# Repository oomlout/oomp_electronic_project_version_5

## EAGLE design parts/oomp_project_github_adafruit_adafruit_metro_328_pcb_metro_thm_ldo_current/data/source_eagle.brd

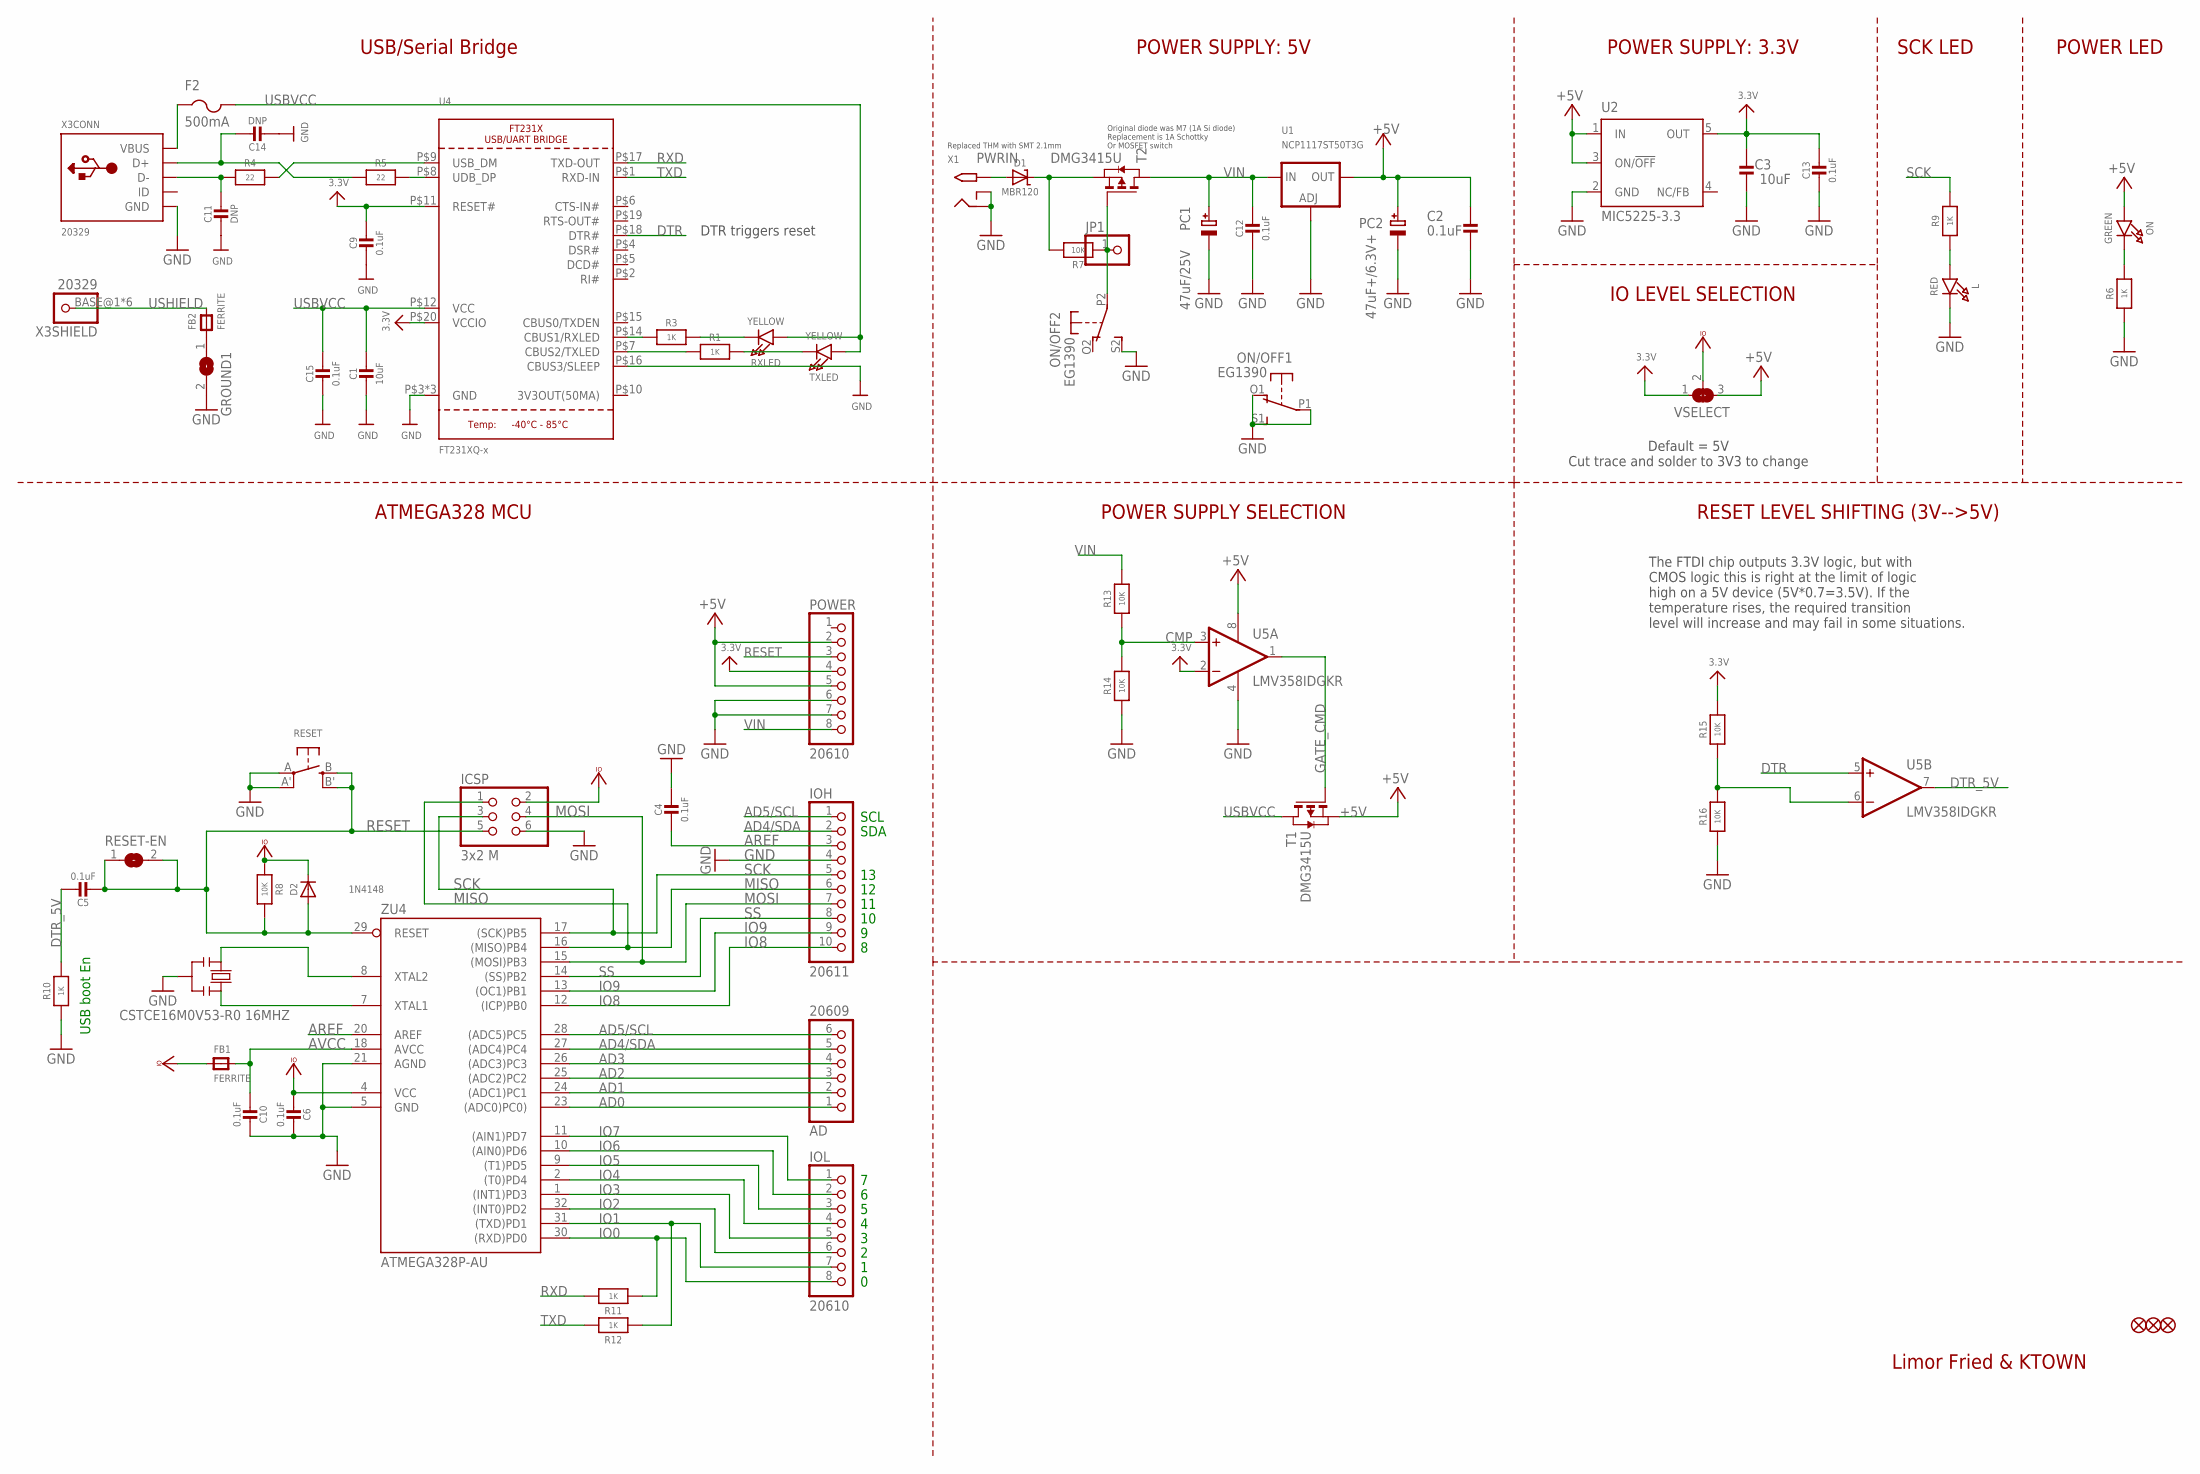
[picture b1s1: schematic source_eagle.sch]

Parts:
AD: 20609; 1X06_OVAL
C1, C3: 10uF; 0805-NO
C2, C4, C5, C6, C9, C12, C13, C15: 0.1uF; 0805-NO
C10: 0.1uF; 0805_10MGAP
C11, C14: DNP; 0805-NO
D1: MBR120; SOD-123
D2: 1N4148; SOD-323
F2: 500mA; R1206
FB1, FB2: FERRITE; 0805-NO
FD1, FD2, FD3: FIDUCIAL""; FIDUCIAL_1MM
GROUND1: SJ
ICSP: 3x2 M; 2X03_ROUND_70MIL
IOH: 20611; 1X10_OVAL
IOL: 20610; 1X08_OVAL
JP1: HEADER-1X1ROUND; 1X01_ROUND
L: RED; CHIPLED_0805_NOOUTLINE
ON: GREEN; CHIPLED_0805_NOOUTLINE
ON/OFF: EG1390
PC1: 47uF/25V; PANASONIC_D
PC2: 47uF+/6.3V+; PANASONIC_D
POWER: 20610; 1X08_OVAL
R1, R3, R6, R9, R10, R11, R12: 1K; 0805-NO
R4, R5: 22; 0805-NO
R7, R13, R14, R15, R16: 10K; 0805-NO
R8: 10K; _0805MP
RESET: SWITCH_TACT_SMT; EVQ-Q2
RESET-EN: SJ
RXLED: YELLOW; CHIPLED_0805_NOOUTLINE
T1, T2: DMG3415U; SOT-23
TXLED: YELLOW; CHIPLED_0805_NOOUTLINE
U1: NCP1117ST50T3G; SOT223-R
U2: MIC5225-3.3; SOT23-DBV
U4: FT231XQ-x; QFN20_4MM
U5: LMV358IDGKR; MSOP08
VSELECT: SOLDERJUMPER_2WAY; SOLDERJUMPER_2WAY_OPEN_NOPASTE
X1: 2.1MMJACKSMT; DCJACK_2MM_SMT
X3: 20329; 4UCONN_20329
Y2: CSTCE16M0V53-R0 16MHZ; RESONATOR
ZU4: ATMEGA328P-AU; TQFP32-08

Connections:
3.3V: C3.2, C9.1, C13.1, POWER.4, R15.2, U2.5 (OUT), U4.P$11 (RESET#), U4.P$20 (VCCIO), U5.2 (-IN), VSELECT.1
3V3OUT(50MA): U4.P$10 (3V3OUT(50MA))
+5V: C2.2, ON.A, PC2.+, POWER.2, POWER.5, T1.2 (S), U1.2 (OUT), U1.4 (OUT), U2.1 (IN), U2.3 (ON/!OFF), U5.8 (V+), VSELECT.3
AD0: AD.1, ZU4.23 ((ADC0)PC0))
AD1: AD.2, ZU4.24 ((ADC1)PC1)
AD2: AD.3, ZU4.25 ((ADC2)PC2)
AD3: AD.4, ZU4.26 ((ADC3)PC3)
AD4/SDA: AD.5, IOH.2, ZU4.27 ((ADC4)PC4)
AD5/SCL: AD.6, IOH.1, ZU4.28 ((ADC5)PC5)
AREF: C4.2, IOH.3, ZU4.20 (AREF)
AVCC: C10.2, FB1.2, ZU4.18 (AVCC)
CMP: R13.1, R14.2, U5.3 (+IN)
D+: C14.1, R5.1, X3.D+
D-: C11.1, R4.1, X3.D-
DTR: U4.P$18 (DTR#), U5.5 (+IN)
DTR_5V: C5.1, R10.2, U5.7 (OUT)
GATE_CMD: T1.3 (G), U5.1 (OUT)
GND: C1.2, C2.1, C3.1, C4.1, C6.1, C9.2, C10.1, C11.2, C12.2, C13.2, C14.2, C15.2, GROUND1.2, ICSP.6, IOH.4, L.C, ON/OFF.O1 (O), ON/OFF.P1, ON/OFF.S1 (S), ON/OFF.S2 (S), PC1.-, PC2.-, POWER.6, POWER.7, R6.1, R10.1, R14.1, R16.1, RESET.A, RESET.A' (P1), U1.1 (ADJ), U2.2 (GND), U4.P$3 (GND), U4.P$13 (GND), U4.P$16 (CBUS3/SLEEP), U4.P$21 (GND), U5.4 (V-), X1.GND (RING), X1.GNDBREAK (RING_SW), X3.GND, Y2.2, ZU4.5 (GND), ZU4.21 (AGND)
IO0: IOL.8, R11.1, ZU4.30 ((RXD)PD0)
IO1: IOL.7, R12.1, ZU4.31 ((TXD)PD1)
IO2: IOL.6, ZU4.32 ((INT0)PD2)
IO3: IOL.5, ZU4.1 ((INT1)PD3)
IO4: IOL.4, ZU4.2 ((T0)PD4)
IO5: IOL.3, ZU4.9 ((T1)PD5)
IO6: IOL.2, ZU4.10 ((AIN0)PD6)
IO7: IOL.1, ZU4.11 ((AIN1)PD7)
IO8: IOH.10, ZU4.12 ((ICP)PB0)
IO9: IOH.9, ZU4.13 ((OC1)PB1)
MISO: ICSP.1, IOH.6, ZU4.16 ((MISO)PB4)
MOSI: ICSP.4, IOH.7, ZU4.15 ((MOSI)PB3)
unnamed: L.A, R9.1
unnamed: FB2.1, GROUND1.1
unnamed: ON.C, R6.2
unnamed: R3.2, U4.P$14 (CBUS1/RXLED)
unnamed: R3.1, RXLED.C
unnamed: R1.2, U4.P$7 (CBUS2/TXLED)
unnamed: R1.1, TXLED.C
unnamed: R4.2, U4.P$9 (USB_DM)
unnamed: R5.2, U4.P$8 (UDB_DP)
unnamed: R15.1, R16.2, U5.6 (-IN)
unnamed: JP1.1, ON/OFF.P2, R7.1, T2.3 (G)
unnamed: D1.C, R7.2, T2.2 (S)
PWRIN: D1.A, X1.PWR2 (TIP)
RESET: C5.2, D2.A, ICSP.5, POWER.3, R8.1, RESET.B (S), RESET.B' (S1), RESET-EN.1, RESET-EN.2, ZU4.29 (RESET)
RXD: R11.2, U4.P$17 (TXD-OUT)
SCK: ICSP.3, IOH.5, R9.2, ZU4.17 ((SCK)PB5)
SS: IOH.8, ZU4.14 ((SS)PB2)
TXD: R12.2, U4.P$1 (RXD-IN)
USBVCC: C1.1, C15.1, F2.2, RXLED.A, T1.1 (D), TXLED.A, U4.P$12 (VCC)
USHIELD: FB2.2, X3.BASE@1 (1), X3.BASE@2 (1), X3.SPRT@1 (1), X3.SPRT@2 (1), X3.SPRT@3 (1), X3.SPRT@4 (1)
VBUS: F2.1, X3.VBUS
VCCIO: C6.2, D2.C, FB1.1, ICSP.2, R8.2, VSELECT.2, ZU4.4 (VCC)
VIN: C12.1, PC1.+, POWER.8, R13.2, T2.1 (D), U1.3 (IN)
XTAL1: Y2.3, ZU4.7 (XTAL1)
XTAL2: Y2.1, ZU4.8 (XTAL2)

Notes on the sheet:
USB boot En
SDA
SCL
Limor Fried & KTOWN
Original diode was M7 (1A Si diode) Replacement is 1A Schottky Or MOSFET switch
Replaced THM with SMT 2.1mm
POWER SUPPLY: 5V
USB/Serial Bridge
POWER SUPPLY: 3.3V
IO LEVEL SELECTION
POWER LED
ATMEGA328 MCU
POWER SUPPLY SELECTION
SCK LED
Default = 5V Cut trace and solder to 3V3 to change
RESET LEVEL SHIFTING (3V-->5V)
The FTDI chip outputs 3.3V logic, but with CMOS logic this is right at the limit of logic high on a 5V device (5V*0.7=3.5V). If the temperature rises, the required transition level will increase and may fail in some situations.
DTR triggers reset

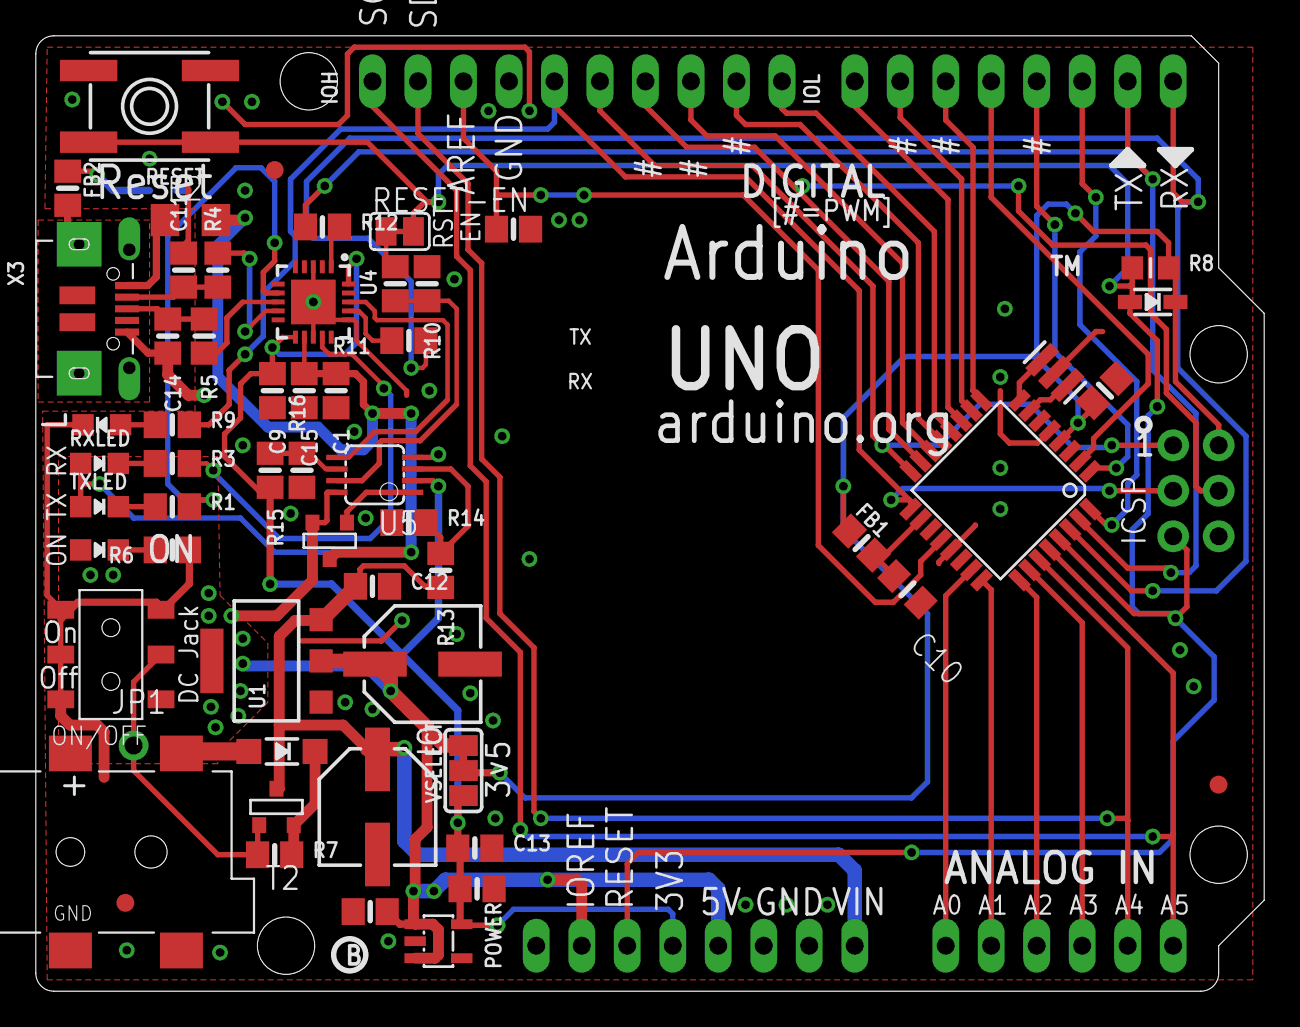
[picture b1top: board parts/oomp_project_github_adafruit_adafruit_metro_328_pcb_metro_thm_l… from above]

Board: 2 copper layers, 68.6 x 53.3 mm, 66 parts (1 on the bottom side), 54 nets.

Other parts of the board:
U$11: METROSILK_TOP
U$14: METROSILK_BOT
U$15: PCBFEAT-REV-040

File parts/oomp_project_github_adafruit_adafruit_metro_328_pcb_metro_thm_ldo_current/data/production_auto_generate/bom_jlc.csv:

Comment,Designator,Footprint,LCSC Part #
,JP1,Metro THM+LDO Rev B-import-fps:1X01_ROUND,C7501259
,RESET0,Metro THM+LDO Rev B-import-fps:EVQ-Q2,
,U$14,Metro THM+LDO Rev B-import-fps:METROSILK_BOT,
,U$11,Metro THM+LDO Rev B-import-fps:METROSILK_TOP,
,U$15,Metro THM+LDO Rev B-import-fps:PCBFEAT-REV-040,
,"GROUND1,RESET-EN0",Metro THM+LDO Rev B-import-fps:SJ,
,VSELECT0,Metro THM+LDO Rev B-import-fps:SOLDERJUMPER_2WAY_OPEN_NOPASTE,
0.1uF,"C2,C4,C5,C6,C9,C12,C13,C15",Metro THM+LDO Rev B-import-fps:0805-NO,
0.1uF,C10,Metro THM+LDO Rev B-import-fps:0805_10MGAP,
10K,"R7,R13,R14,R15,R16",Metro THM+LDO Rev B-import-fps:0805-NO,C17414
10K,R8,Metro THM+LDO Rev B-import-fps:_0805MP,C17414
10uF,"C1,C3",Metro THM+LDO Rev B-import-fps:0805-NO,
1K,"R1,R3,R6,R9,R10,R11,R12",Metro THM+LDO Rev B-import-fps:0805-NO,C17513
1N4148,D2,Metro THM+LDO Rev B-import-fps:SOD-323,
2.1MMJACKSMT,X1,Metro THM+LDO Rev B-import-fps:DCJACK_2MM_SMT,
20329,X3,Metro THM+LDO Rev B-import-fps:4UCONN_20329,
20609,AD0,Metro THM+LDO Rev B-import-fps:1X06_OVAL,C37208
20610,"IOL0,POWER0",Metro THM+LDO Rev B-import-fps:1X08_OVAL,C492421
20611,IOH0,Metro THM+LDO Rev B-import-fps:1X10_OVAL,C57369
22,"R4,R5",Metro THM+LDO Rev B-import-fps:0805-NO,C2907310
3x2 M,ICSP0,Metro THM+LDO Rev B-import-fps:2X03_ROUND_70MIL,
47uF+/6.3V+,PC2,Metro THM+LDO Rev B-import-fps:PANASONIC_D,
47uF/25V,PC1,Metro THM+LDO Rev B-import-fps:PANASONIC_D,
500mA,F2,Metro THM+LDO Rev B-import-fps:R1206,
ATMEGA328P-AU,ZU4,Metro THM+LDO Rev B-import-fps:TQFP32-08,
CSTCE16M0V53-R0 16MHZ,Y2,Metro THM+LDO Rev B-import-fps:RESONATOR,
DMG3415U,"T1,T2",Metro THM+LDO Rev B-import-fps:SOT-23,
DNP,"C11,C14",Metro THM+LDO Rev B-import-fps:0805-NO,
EG1390,ON/OFF0,Metro THM+LDO Rev B-import-fps:EG1390,
FERRITE,"FB1,FB2",Metro THM+LDO Rev B-import-fps:0805-NO,
"FIDUCIAL""""","FD1,FD2,FD3",Metro THM+LDO Rev B-import-fps:FIDUCIAL_1MM,
FT231XQ-x ,U4,Metro THM+LDO Rev B-import-fps:QFN20_4MM,
GREEN,ON0,Metro THM+LDO Rev B-import-fps:CHIPLED_0805_NOOUTLINE,
LMV358IDGKR,U5,Metro THM+LDO Rev B-import-fps:MSOP08,
MBR120,D1,Metro THM+LDO Rev B-import-fps:SOD-123,
MIC5225-3.3,U2,Metro THM+LDO Rev B-import-fps:SOT23-DBV,
NCP1117ST50T3G,U1,Metro THM+LDO Rev B-import-fps:SOT223-R,
RED,L0,Metro THM+LDO Rev B-import-fps:CHIPLED_0805_NOOUTLINE,
YELLOW,"RXLED0,TXLED0",Metro THM+LDO Rev B-import-fps:CHIPLED_0805_NOOUTLINE,

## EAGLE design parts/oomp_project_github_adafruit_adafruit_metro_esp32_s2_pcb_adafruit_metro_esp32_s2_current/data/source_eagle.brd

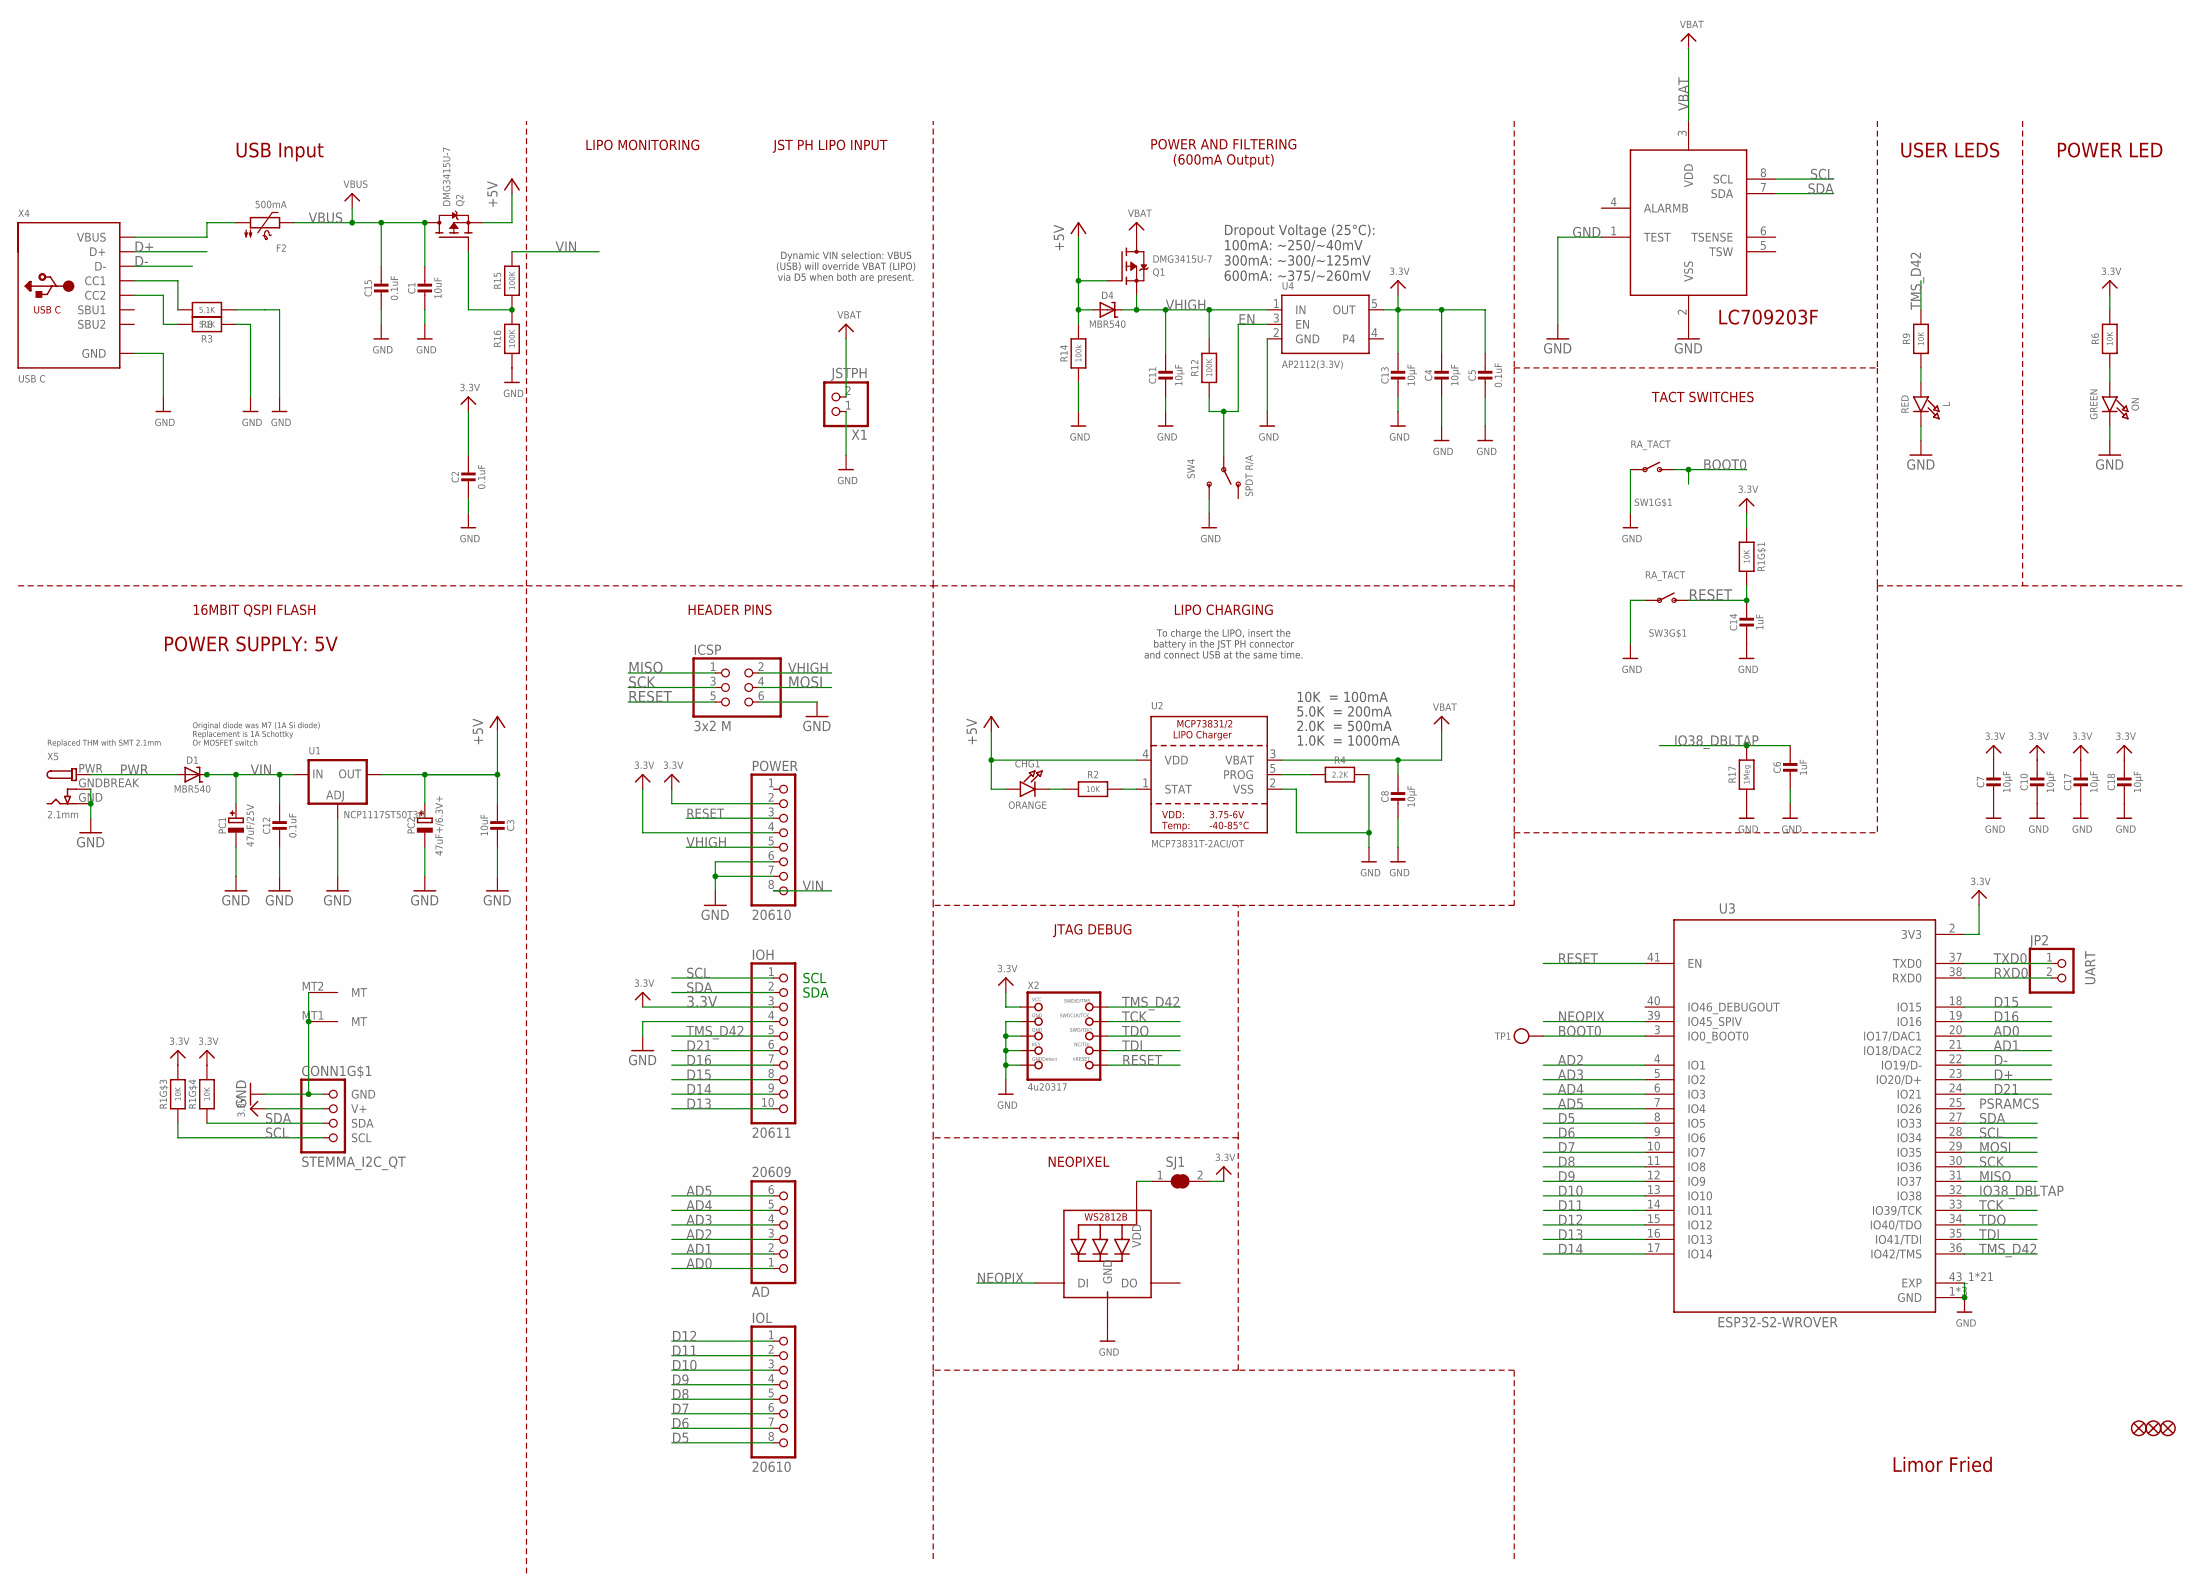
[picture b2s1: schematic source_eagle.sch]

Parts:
AD: 20609; 1X06_OVALWAVE
C1, C3: 10uF; 0805-NO
C2, C5, C12, C15: 0.1uF; 0603-NO
C4, C7, C8, C10, C11, C13, C17, C18: 10µF; 0805-NO
C6, C14: 1uF; 0603-NO
CHG1: ORANGE; CHIPLED_0603_NOOUTLINE
CONN1: STEMMA_I2C_QT; JST_SH4
D1, D4: MBR540; SOD-123
F2: 500mA; 1206
FD1, FD2, FD3: FIDUCIAL_1MM
IC2: LC709203F; WDFN8_3X4_0.65
ICSP: 3x2 M; 2X03_ROUND_70MIL
IOH: 20611; 1X10_OVALWAVE
IOL: 20610; 1X08_OVALWAVE
JP2: UART; 1X02_ROUND
L: RED; CHIPLED_0603_NOOUTLINE
LED1: WS2812B3535; LED3535
ON: GREEN; CHIPLED_0603_NOOUTLINE
PC1: 47uF/25V; PANASONIC_D
PC2: 47uF+/6.3V+; PANASONIC_D
POWER: 20610; 1X08_OVALWAVE
Q1, Q2: DMG3415U-7; SOT23-R
R1: 10K; RESPACK_4X0603
R2, R6, R9: 10K; 0603-NO
R3, R8: 5.1K; 0603-NO
R4: 2.2K; 0603-NO
R12, R15, R16: 100K; 0603-NO
R14: 100k; 0603-NO
R17: 1Meg; 0603-NO
SJ1: SOLDERJUMPER_CLOSED; SOLDERJUMPER_CLOSEDWIRE
SW1, SW3: RA_TACT; SPST_TACTILE_RA
SW4: SPDT R/A; SPDT_SMT_SSSS811101
TP1: TESTPOINTROUND1.5MMNO; TESTPOINT_ROUND_1.5MM_NO
U1: NCP1117ST50T3G; SOT223-R
U2: MCP73831T-2ACI/OT; SOT23-5
U3: ESP32-S2-WROVER; MODULE_ESP32-S2-WROVER
U4: AP2112(3.3V); SOT23-5
X1: JSTPH; JSTPH2_BATT
X2: 4u20317; 2X05_1.27MM_BOX_POSTS
X4: USB C; USB_C_CUSB31-CFM2AX-01-X
X5: 2.1mm; DCJACK_2MM_PTH

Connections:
3.3V: C2.1, C4.1, C5.1, C7.1, C10.1, C13.1, C17.1, C18.1, CONN1.2 (V+), IOH.3, POWER.2, POWER.4, R1.1, R1.5 (2), R1.6 (2), R6.2, SJ1.2, U3.2 (3V3), U4.5 (OUT), X2.1 (VCC)
+5V: C3.2, CHG1.A, D4.A, PC2.+, Q1.1 (G), Q2.2 (S), R14.2, U1.2 (OUT), U1.4 (OUT), U2.4 (VDD)
AD0: AD.1, U3.20 (IO17/DAC1)
AD1: AD.2, U3.21 (IO18/DAC2)
AD2: AD.3, U3.4 (IO1)
AD3: AD.4, U3.5 (IO2)
AD4: AD.5, U3.6 (IO3)
AD5: AD.6, U3.7 (IO4)
BOOT0: SW1.2 (S), TP1.P$1, U3.3 (IO0_BOOT0)
D5: IOL.8, U3.8 (IO5)
D6: IOL.7, U3.9 (IO6)
D7: IOL.6, U3.10 (IO7)
D8: IOL.5, U3.11 (IO8)
D9: IOL.4, U3.12 (IO9)
D10: IOL.3, U3.13 (IO10)
D11: IOL.2, U3.14 (IO11)
D12: IOL.1, U3.15 (IO12)
D13: IOH.10, U3.16 (IO13)
D14: IOH.9, U3.17 (IO14)
D15: IOH.8, U3.18 (IO15)
D16: IOH.7, U3.19 (IO16)
D21: IOH.6, U3.24 (IO21)
D+: U3.23 (IO20/D+), X4.A6 (D+), X4.B6 (D+)
D-: U3.22 (IO19/D-), X4.A7 (D-), X4.B7 (D-)
EN: R12.1, SW4.B, U4.3 (EN)
GND: C1.2, C2.2, C3.1, C4.2, C5.2, C6.2, C7.2, C8.2, C10.2, C11.2, C12.2, C13.2, C14.2, C15.2, C17.2, C18.2, CONN1.1 (GND), CONN1.MT1 (MT), CONN1.MT2 (MT), IC2.1 (TEST), IC2.2 (VSS), ICSP.6, IOH.4, L.C, LED1.4 (GND), ON.C, PC1.-, PC2.-, POWER.6, POWER.7, R3.1, R4.2, R8.1, R14.1, R16.1, R17.1, SW1.1, SW3.1, SW4.C (S), U1.1 (ADJ), U2.2 (VSS), U3.1 (GND), U3.26 (GND), U3.42 (GND), U3.43_1 (EXP), U3.43_2 (EXP), U3.43_3 (EXP), U3.43_4 (EXP), U3.43_5 (EXP), U3.43_6 (EXP), U3.43_7 (EXP), U3.43_8 (EXP), U3.43_9 (EXP), U3.43_10 (EXP), U3.43_11 (EXP), U3.43_12 (EXP), U3.43_13 (EXP), U3.43_14 (EXP), U3.43_15 (EXP), U3.43_16 (EXP), U3.43_17 (EXP), U3.43_18 (EXP), U3.43_19 (EXP), U3.43_20 (EXP), U3.43_21 (EXP), U4.2 (GND), X1.1, X2.3 (GND), X2.5 (GND), X2.7 (KEY), X2.9 (GNDDETECT), X4.A1B12 (GND), X4.B1A12 (GND), X5.GND, X5.GNDBREAK
IO38_DBLTAP: C6.1, R17.2, U3.32 (IO38)
MISO: ICSP.1, U3.31 (IO37)
MOSI: ICSP.4, U3.29 (IO35)
unnamed: L.A, R9.1
unnamed: Q2.1 (G), R15.1, R16.2
unnamed: ON.A, R6.1
unnamed: CHG1.C, R2.1
unnamed: LED1.2 (VDD), SJ1.1
unnamed: R2.2, U2.1 (STAT)
unnamed: R8.2, X4.A5 (CC1)
unnamed: R3.2, X4.B5 (CC2)
unnamed: R4.1, U2.5 (PROG)
unnamed: F2.1, X4.A4B9 (VBUS), X4.B4A9 (VBUS)
NEOPIX: LED1.1 (DI), U3.39 (IO45_SPIV)
PWR: D1.A, X5.PWR
RESET: C14.1, ICSP.5, POWER.3, R1.8 (2), SW3.2 (S), U3.41 (EN), X2.10 (NRESET)
RXD0: JP2.2, U3.38 (RXD0)
SCK: ICSP.3, U3.30 (IO36)
SCL: CONN1.4 (SCL), IC2.8 (SCL), IOH.1, R1.3 (1), U3.28 (IO34)
SDA: CONN1.3 (SDA), IC2.7 (SDA), IOH.2, R1.4 (1), U3.27 (IO33)
TCK: U3.33 (IO39/TCK), X2.4 (SWDCLK)
TDI: U3.35 (IO41/TDI), X2.8 (TDI)
TDO: U3.34 (IO40/TDO), X2.6 (SWO)
TMS_D42: IOH.5, R9.2, U3.36 (IO42/TMS), X2.2 (SWDIO)
TXD0: JP2.1, U3.37 (TXD0)
VBAT: C8.1, IC2.3 (VDD), Q1.3 (D), U2.3 (VBAT), X1.2
VBUS: C1.1, C15.1, F2.2, Q2.3 (D)
VHIGH: C11.1, D4.C, ICSP.2, POWER.5, Q1.2 (S), R12.2, U4.1 (IN)
VIN: C12.1, D1.C, PC1.+, POWER.8, R15.2, U1.3 (IN)

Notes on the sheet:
SDA
SCL
Limor Fried
USB Input
POWER LED
USER LEDS
10K = 100mA
5.0K = 200mA
2.0K = 500mA
1.0K = 1000mA
LIPO CHARGING
LIPO MONITORING
To charge the LIPO, insert the battery in the JST PH connector and connect USB at the same time.
POWER AND FILTERING (600mA Output)
JST PH LIPO INPUT
Dynamic VIN selection: VBUS (USB) will override VBAT (LIPO) via D5 when both are present.
Dropout Voltage (25°C): 100mA: ~250/~40mV 300mA: ~300/~125mV 600mA: ~375/~260mV
HEADER PINS
16MBIT QSPI FLASH
TACT SWITCHES
JTAG DEBUG
NEOPIXEL
Original diode was M7 (1A Si diode) Replacement is 1A Schottky Or MOSFET switch
Replaced THM with SMT 2.1mm
POWER SUPPLY: 5V
PSRAMCS

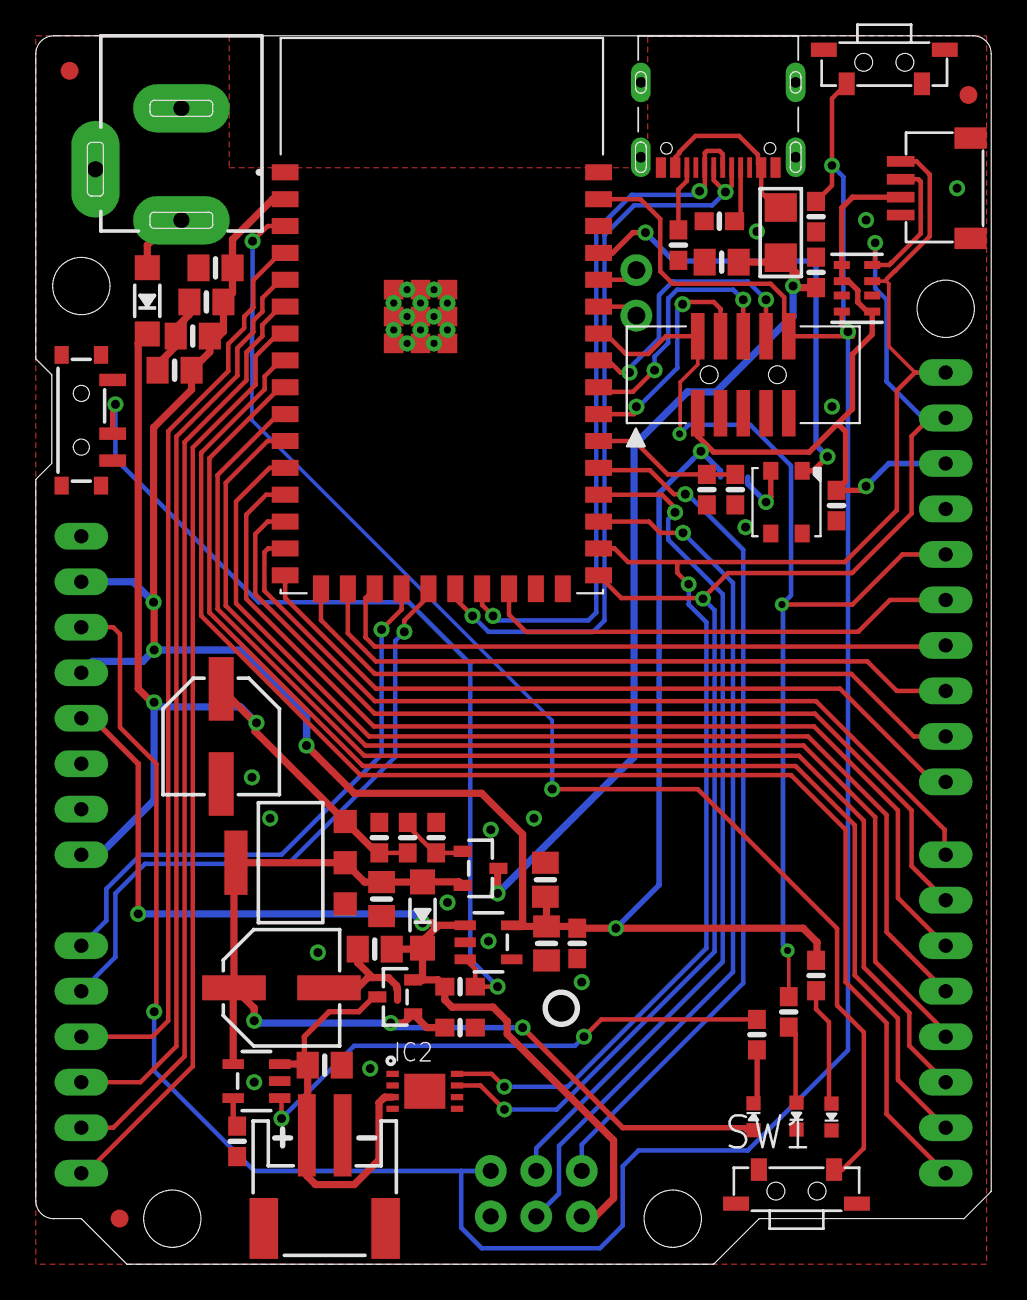
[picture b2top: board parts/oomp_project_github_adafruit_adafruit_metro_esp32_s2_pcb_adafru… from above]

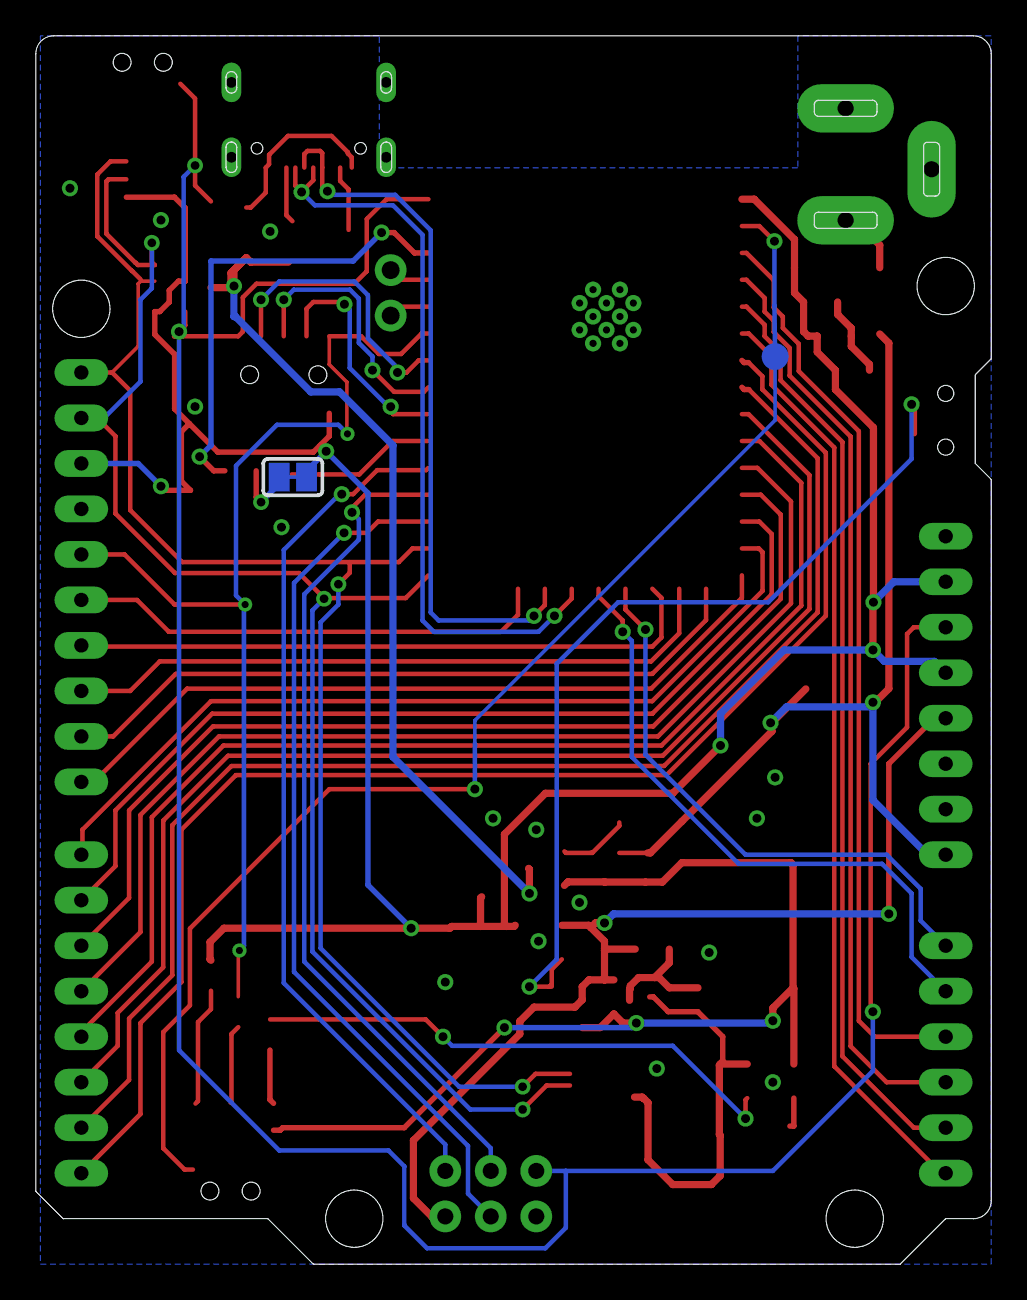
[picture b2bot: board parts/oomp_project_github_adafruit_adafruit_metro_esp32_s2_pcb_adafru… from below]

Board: 2 copper layers, 53.3 x 68.6 mm, 66 parts (3 on the bottom side), 55 nets.

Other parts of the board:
U$15: PCBFEAT-REV-040
U$52: ESP32S2_TOP
U$53: ESP32S2_BOT

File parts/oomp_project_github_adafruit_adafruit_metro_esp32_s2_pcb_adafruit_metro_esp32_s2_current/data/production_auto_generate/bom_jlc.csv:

Comment,Designator,Footprint,LCSC Part #
,U$53,Adafruit Metro ESP32-S2-import-fps:ESP32S2_BOT,
,U$52,Adafruit Metro ESP32-S2-import-fps:ESP32S2_TOP,
,U$15,Adafruit Metro ESP32-S2-import-fps:PCBFEAT-REV-040,
,TP1,Adafruit Metro ESP32-S2-import-fps:TESTPOINT_ROUND_1.5MM_NO,
0.1uF,"C2,C5,C12,C15",Adafruit Metro ESP32-S2-import-fps:0603-NO,C14663
100K,"R12,R15,R16",Adafruit Metro ESP32-S2-import-fps:0603-NO,C25803
100k,R14,Adafruit Metro ESP32-S2-import-fps:0603-NO,C25803
10K,"R2,R6,R9",Adafruit Metro ESP32-S2-import-fps:0603-NO,C98220
10K,R1,Adafruit Metro ESP32-S2-import-fps:RESPACK_4X0603,C98220
10uF,"C1,C3",Adafruit Metro ESP32-S2-import-fps:0805-NO,
10µF,"C4,C7,C8,C10,C11,C13,C17,C18",Adafruit Metro ESP32-S2-import-fps:0805-NO,
1Meg,R17,Adafruit Metro ESP32-S2-import-fps:0603-NO,C2907003
1uF,"C6,C14",Adafruit Metro ESP32-S2-import-fps:0603-NO,C5673
2.1mm,X5,Adafruit Metro ESP32-S2-import-fps:DCJACK_2MM_PTH,
2.2K,R4,Adafruit Metro ESP32-S2-import-fps:0603-NO,C4190
20609,AD0,Adafruit Metro ESP32-S2-import-fps:1X06_OVALWAVE,C37208
20610,"IOL0,POWER0",Adafruit Metro ESP32-S2-import-fps:1X08_OVALWAVE,C492421
20611,IOH0,Adafruit Metro ESP32-S2-import-fps:1X10_OVALWAVE,C57369
3x2 M,ICSP0,Adafruit Metro ESP32-S2-import-fps:2X03_ROUND_70MIL,
47uF+/6.3V+,PC2,Adafruit Metro ESP32-S2-import-fps:PANASONIC_D,
47uF/25V,PC1,Adafruit Metro ESP32-S2-import-fps:PANASONIC_D,
4u20317,X2,Adafruit Metro ESP32-S2-import-fps:2X05_1.27MM_BOX_POSTS,
5.1K,"R3,R8",Adafruit Metro ESP32-S2-import-fps:0603-NO,C23186
500mA,F2,Adafruit Metro ESP32-S2-import-fps:1206,
AP2112(3.3V),U4,Adafruit Metro ESP32-S2-import-fps:SOT23-5,
DMG3415U-7,"Q1,Q2",Adafruit Metro ESP32-S2-import-fps:SOT23-R,
ESP32-S2-WROVER,U3,Adafruit Metro ESP32-S2-import-fps:MODULE_ESP32-S2-WROVER,
FIDUCIAL_1MM,"FD1,FD2,FD3",Adafruit Metro ESP32-S2-import-fps:FIDUCIAL_1MM,
GREEN,ON0,Adafruit Metro ESP32-S2-import-fps:CHIPLED_0603_NOOUTLINE,
JSTPH,X1,Adafruit Metro ESP32-S2-import-fps:JSTPH2_BATT,
LC709203F,IC2,Adafruit Metro ESP32-S2-import-fps:WDFN8_3X4_0.65,
MBR540,"D1,D4",Adafruit Metro ESP32-S2-import-fps:SOD-123,
MCP73831T-2ACI/OT,U2,Adafruit Metro ESP32-S2-import-fps:SOT23-5,
NCP1117ST50T3G,U1,Adafruit Metro ESP32-S2-import-fps:SOT223-R,
ORANGE,CHG1,Adafruit Metro ESP32-S2-import-fps:CHIPLED_0603_NOOUTLINE,
RA_TACT,"SW1,SW3",Adafruit Metro ESP32-S2-import-fps:SPST_TACTILE_RA,
RED,L0,Adafruit Metro ESP32-S2-import-fps:CHIPLED_0603_NOOUTLINE,
SPDT R/A,SW4,Adafruit Metro ESP32-S2-import-fps:SPDT_SMT_SSSS811101,
STEMMA_I2C_QT,CONN1,Adafruit Metro ESP32-S2-import-fps:JST_SH4,C160404
UART,JP2,Adafruit Metro ESP32-S2-import-fps:1X02_ROUND,C492401
USB C,X4,Adafruit Metro ESP32-S2-import-fps:USB_C_CUSB31-CFM2AX-01-X,
WS2812B3535,LED1,Adafruit Metro ESP32-S2-import-fps:LED3535,

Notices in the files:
parts and their libraries:
microbuilder: This work is placed in the public domain, and may be freely used for commercial and non-commercial work with the following conditions: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
SparkFun-Aesthetics: Licensing: CC v3.0 Share-Alike You are welcome to use this library for commercial purposes.
